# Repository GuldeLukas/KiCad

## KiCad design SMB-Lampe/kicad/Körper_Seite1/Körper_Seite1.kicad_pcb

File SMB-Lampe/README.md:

# README – SMB-Lampe (KiCad-Projekt)

- **Version / Stand:** 09.03.26
- **Verantwortliche Person / Team:** Lukas Gulde
- **Softwareversionen:** verwendete KiCad-Version 9.0
- **Fertigungsstatus:** Prototyp, Dokumentation nicht abgeschlossen
- **Lizenz / Nutzungsrechte:** 
- **Änderungshistorie:** 

## Projektübersicht
Dieses Verzeichnis enthält die Konstruktionsdaten des Projekts **SMB-Lampe**. Die Dateien liegen als **KiCad-Projekte** vor und umfassen Schaltpläne, Platinenentwürfe sowie projektbezogene Bibliotheken und Zusatzdateien.

## Speicherort der Projektdateien
Die relevanten Projektdateien des Programms **SMB-Lampe** sind unter folgendem Pfad verzeichnet:

- `KiCad-master/SMB-Lampe/kicad/`

Dort befinden sich unter anderem die Hauptprojektdateien:

- `SMB-Lampe.kicad_pro` – KiCad-Projektdatei

## Teilprojekte / Unterordner für Platinenentwürfe
Die jeweiligen Schaltpläne und Platinenentwürfe der einzelnen Baugruppen befinden sich in den folgenden Unterordnern:

- `Hauptplatine`
- `Hinterbein_hinten_Seite1_LED-P`
- `Hinterbein_hinten_Seite2_LED-P`
- `Hinterbein_vorne_Seite1_LED-P`
- `Hinterbein_vorne_Seite2_LED-P`
- `Körper_Seite1` 
- `Körper_Seite2` 

In diesen Ordnern liegen jeweils die zugehörigen KiCad-Dateien, typischerweise:

- `*.kicad_pro` – Projektdatei
- `*.kicad_sch` – Schaltplan
- `*.kicad_pcb` – Platinenlayout
- `*.kicad_prl` – projektspezifische Layout-/Darstellungseinstellungen

Teilweise sind zusätzlich weitere Fertigungs- oder 3D-Daten vorhanden, z. B.:

- `*.step` – 3D-Modell
- `*.gbrjob` – Gerber-Jobdatei

## Bibliotheken und Zusatzdaten
Zusätzliche projektbezogene Bibliotheken und Referenzdaten befinden sich in folgenden Verzeichnissen:

- `KiCad-master/Lib/` – benutzerdefinierte Bibliotheken
- `KiCad-master/Footprints/` – Footprint-Bibliotheken
- `KiCad-master/Datasheet/` – Datenblätter und Referenzunterlagen

Diese Ordner können für das korrekte Laden von Symbolen, Footprints und Zusatzinformationen in KiCad erforderlich sein.

## Empfohlene Verwendung
Zum Öffnen des Projekts wird **KiCad 9.x** empfohlen. Vorgehensweise:

1. KiCad starten.
2. Die Datei `SMB-Lampe.kicad_pro` öffnen.
3. Für einzelne Baugruppen bei Bedarf die jeweilige `*.kicad_pro`-Datei im entsprechenden Unterordner öffnen.

## Zweck dieses README
Dieses README dient der schnellen Orientierung innerhalb der Projektstruktur und erleichtert das Auffinden von:

- Hauptprojektdatei
- Schaltplänen
- Platinenlayouts
- Teilprojekten einzelner Baugruppen
- Bibliotheken und Zusatzdateien

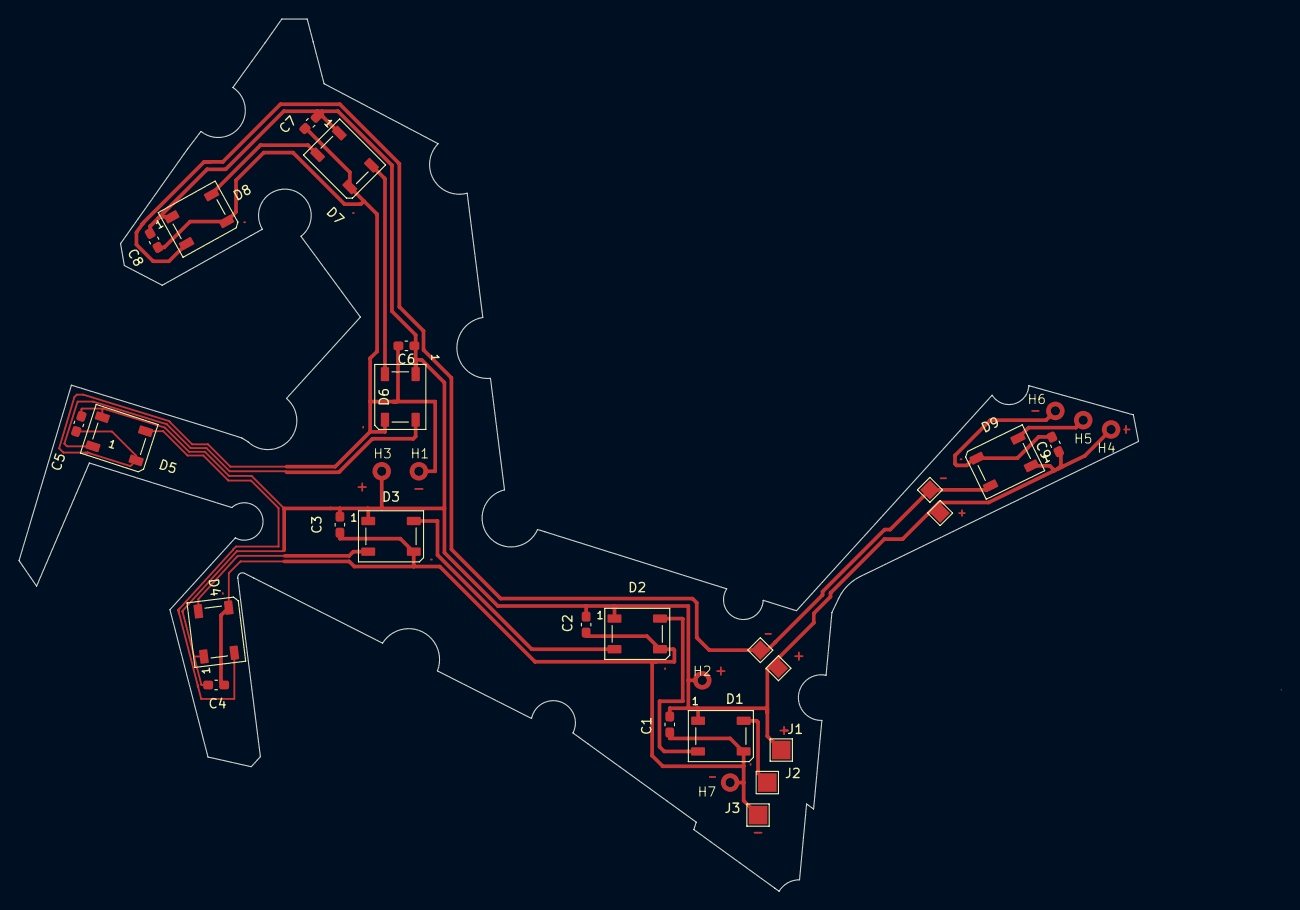
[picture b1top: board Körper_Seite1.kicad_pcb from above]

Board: 2 copper layers, 120.5 x 93.9 mm, 28 parts (0 on the bottom side), 12 nets.

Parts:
C1, C2, C3, C4, C5, C6, C7, C8, C9: 100nF; C_0603_1608Metric_Pad1.08x0.95mm_HandSolder
D1, D2, D3, D4, D5, D6, D7, D8, D9: WS2812B; LED_WS2812B_PLCC4_5.0x5.0mm_P3.2mm
H1, H2, H3, H4, H5, H6, H7: MountingHole_Pad; MountingHole D2 x d1 test
J1, J2, J3: Conn_01x01_Pin; TestPoint_Pad_2.0x2.0mm

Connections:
+5V: C1.1, C2.1, C3.1, C4.1, C5.1, C6.1, C7.1, C8.1, C9.1, D1.1 (VDD), D2.1 (VDD), D3.1 (VDD), D4.1 (VDD), D5.1 (VDD), D6.1 (VDD), D7.1 (VDD), D8.1 (VDD), D9.1 (VDD), H2.1, H3.1, H4.1, J1.1
/Data_In__Hinterbein_hinten_Seite2: D1.4 (DIN), J2.1
/Data_OUT_Körper_Seite2: D9.2 (DOUT), H5.1
Data: D5.2 (DOUT), D6.4 (DIN)
GND: C1.2, C2.2, C3.2, C4.2, C5.2, C6.2, C7.2, C8.2, C9.2, D1.3 (VSS), D2.3 (VSS), D3.3 (VSS), D4.3 (VSS), D5.3 (VSS), D6.3 (VSS), D7.3 (VSS), D8.3 (VSS), D9.3 (VSS), H1.1, H6.1, H7.1, J3.1
unnamed: D1.2 (DOUT), D2.4 (DIN)
unnamed: D2.2 (DOUT), D3.4 (DIN)
unnamed: D3.2 (DOUT), D4.4 (DIN)
unnamed: D4.2 (DOUT), D5.4 (DIN)
unnamed: D6.2 (DOUT), D7.4 (DIN)
unnamed: D7.2 (DOUT), D8.4 (DIN)
unnamed: D8.2 (DOUT), D9.4 (DIN)

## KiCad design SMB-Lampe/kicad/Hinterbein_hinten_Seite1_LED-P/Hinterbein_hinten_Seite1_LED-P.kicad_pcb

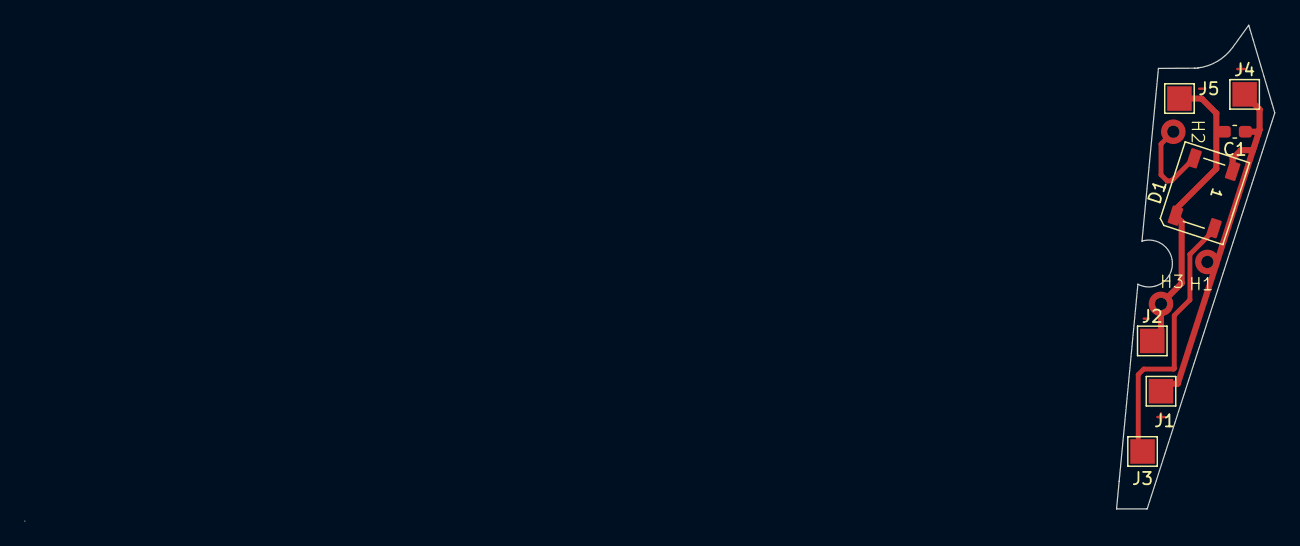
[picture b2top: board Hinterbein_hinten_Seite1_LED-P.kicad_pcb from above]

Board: 2 copper layers, 12.9 x 39.3 mm, 10 parts (0 on the bottom side), 4 nets.

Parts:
C1: 100nF; C_0603_1608Metric_Pad1.08x0.95mm_HandSolder
D1: WS2812B; LED_WS2812B_PLCC4_5.0x5.0mm_P3.2mm
H1, H2, H3: MountingHole_Pad; MountingHole D2 x d1 test
J1, J2, J3, J4, J5: Conn_01x01_Pin; TestPoint_Pad_2.0x2.0mm

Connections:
/+5V_IN_Hauptplatine: C1.1, D1.1 (VDD), H1.1, J1.1, J4.1
/Data_IN_Hauptplatine: D1.4 (DIN), J3.1
/Data_OUT_Hinterbein_hinten_Seite2: D1.2 (DOUT), H2.1
GND: C1.2, D1.3 (VSS), H3.1, J2.1, J5.1

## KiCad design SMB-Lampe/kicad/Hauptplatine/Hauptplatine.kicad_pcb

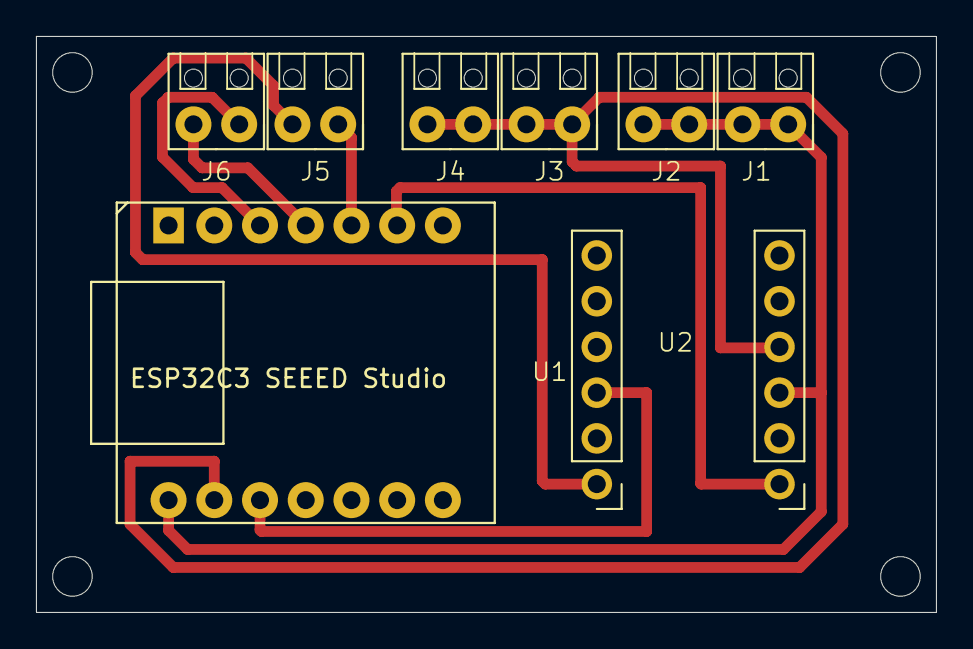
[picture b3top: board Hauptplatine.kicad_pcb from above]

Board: 2 copper layers, 50.0 x 32.0 mm, 8 parts (0 on the bottom side), 8 nets.

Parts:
J1, J2, J3, J4, J5, J6: Screw_Terminal_01x02; Screw Terminal
U1: ESP32C3 SEEED Studio; ESP32 C3
U2: 4-Kanal-I2C Pegelwandler; I2C Levelshifter

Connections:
+3.3V: U1.12 (3V3), U2.3 (LV)
+5V: J1.1, J1.2, J2.1, J2.2, U1.14 (5V), U2.9 (HV)
/ECHO_Ultraschall: J5.2, U2.1 (LV1)
/TRIG_Ultraschall: J5.1, U1.5 (PA8_A4_D4_SDA)
Data_LED: J6.2, U1.4 (PA11_A3_D3)
GND: J3.1, J3.2, J4.1, J4.2, U1.13 (GND), U2.10 (GND)
unnamed: U1.6 (PA9_A5_D5_SCL), U2.7 (HV1)
Steuer_Servo: J6.1, U1.3 (PA10_A2_D2)

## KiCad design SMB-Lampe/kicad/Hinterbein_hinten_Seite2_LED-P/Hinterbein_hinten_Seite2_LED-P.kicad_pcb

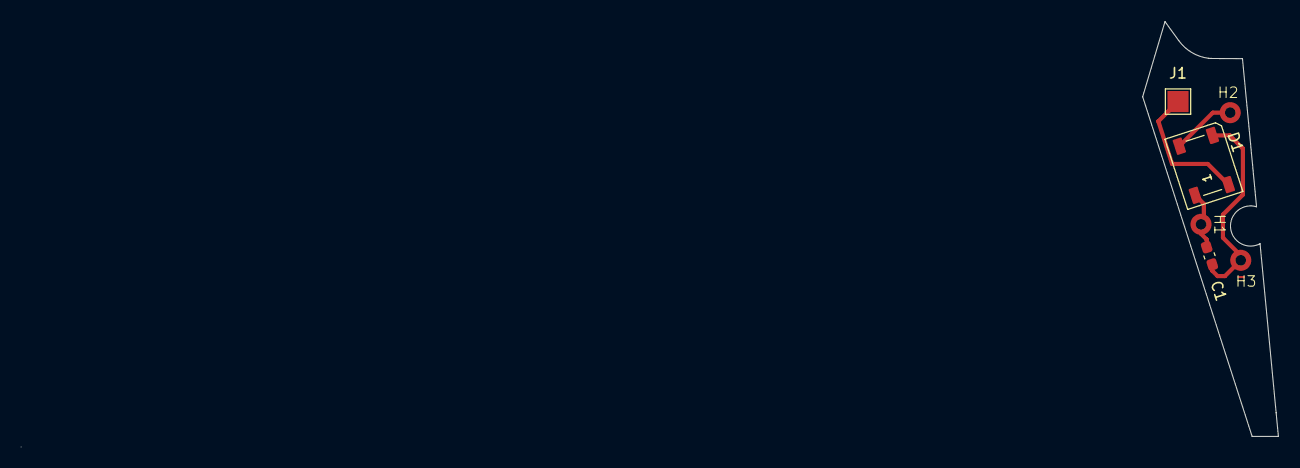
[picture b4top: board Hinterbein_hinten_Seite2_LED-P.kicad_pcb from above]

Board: 2 copper layers, 12.9 x 39.3 mm, 6 parts (0 on the bottom side), 4 nets.

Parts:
C1: 100nF; C_0603_1608Metric_Pad1.08x0.95mm_HandSolder
D1: WS2812B; LED_WS2812B_PLCC4_5.0x5.0mm_P3.2mm
H1, H2, H3: MountingHole_Pad; MountingHole D2 x d1 test
J1: Conn_01x01_Pin; TestPoint_Pad_2.0x2.0mm

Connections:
/+5V_IN_Hinterbein_hinten_Seite1: C1.1, D1.1 (VDD), H1.1
/Data_IN_Hinterbein_hinten_Seite1: D1.4 (DIN), H2.1
/Data_OUT_Körper_Seite1: D1.2 (DOUT), J1.1
GND: C1.2, D1.3 (VSS), H3.1

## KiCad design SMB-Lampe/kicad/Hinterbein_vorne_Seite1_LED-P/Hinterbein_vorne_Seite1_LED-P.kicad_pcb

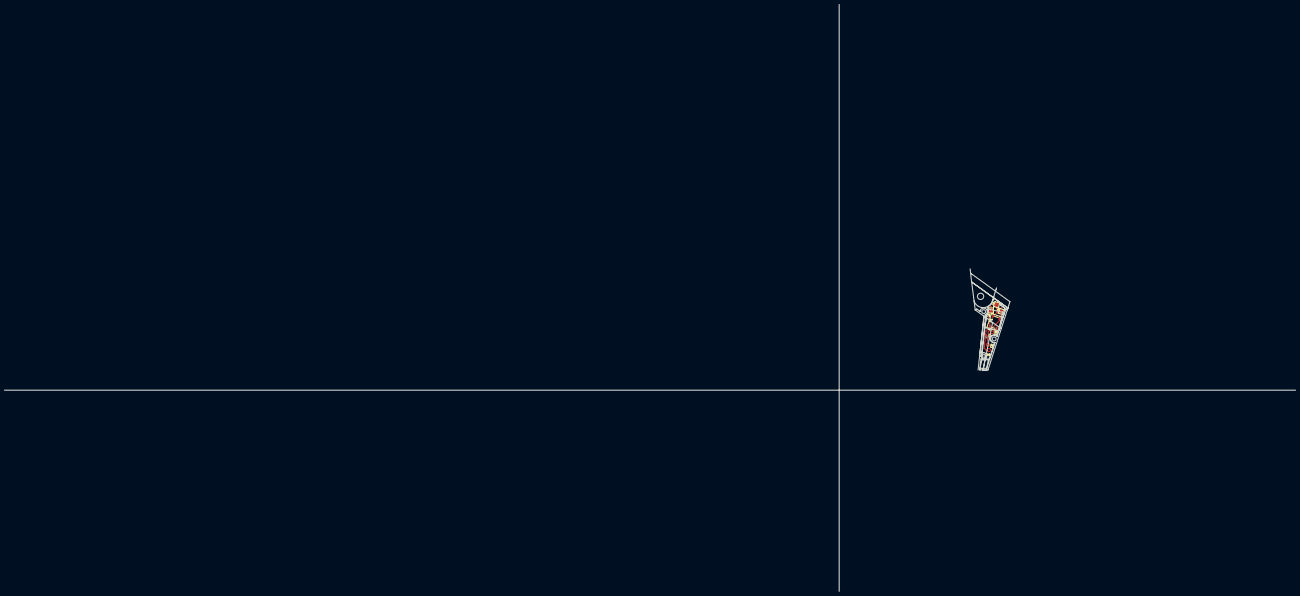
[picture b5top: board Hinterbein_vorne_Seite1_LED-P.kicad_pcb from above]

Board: 2 copper layers, 11.5 x 29.2 mm, 8 parts (0 on the bottom side), 4 nets.

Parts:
C1: 100nF; C_0603_1608Metric_Pad1.08x0.95mm_HandSolder
D1: WS2812B; LED_WS2812B_PLCC4_5.0x5.0mm_P3.2mm
H1, H2, H3: MountingHole_Pad; MountingHole D2 x d1 test
J1, J2, J3: Conn_01x01_Pin; TestPoint_Pad_2.0x2.0mm

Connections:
/+5V_IN_Körper_Seite2: C1.1, D1.1 (VDD), H1.1, J1.1
/Data_IN_Körper_Seite2: D1.4 (DIN), J2.1
/Data_OUT_Hinterbein_vorne_Seite2: D1.2 (DOUT), H2.1
GND: C1.2, D1.3 (VSS), H3.1, J3.1

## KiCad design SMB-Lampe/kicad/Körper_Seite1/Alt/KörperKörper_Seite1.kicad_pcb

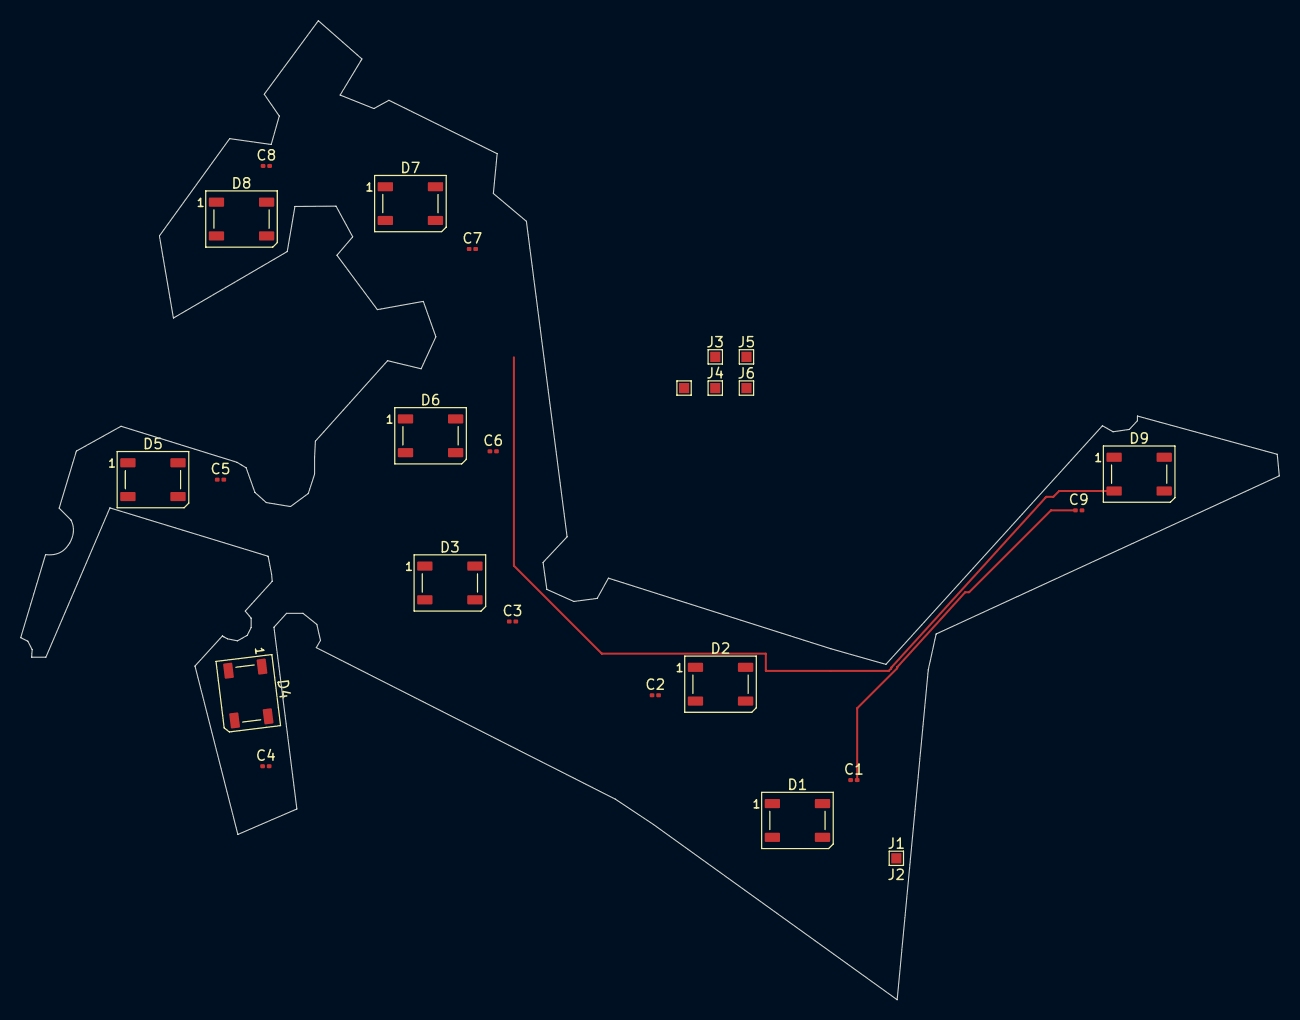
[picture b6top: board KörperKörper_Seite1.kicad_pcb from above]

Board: 2 copper layers, 123.0 x 95.7 mm, 24 parts (0 on the bottom side), 11 nets.

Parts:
C1, C2, C3, C4, C5, C6, C7, C8, C9: 100nF; C_0201_0603Metric
D1, D2, D3, D4, D5, D6, D7, D8, D9: WS2812B; LED_WS2812B_PLCC4_5.0x5.0mm_P3.2mm
J1, J2, J3, J4, J5, J6: Conn_01x01_Pin; TestPoint_Pad_1.0x1.0mm

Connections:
+5V: C1.1, C1.2, C2.1, C2.2, C3.1, C3.2, C4.1, C4.2, C5.1, C5.2, C6.1, C6.2, C7.1, C7.2, C8.1, C8.2, C9.1, C9.2, D1.1 (VDD), D1.3 (VSS), D2.1 (VDD), D2.3 (VSS), D3.1 (VDD), D3.3 (VSS), D4.1 (VDD), D4.3 (VSS), D5.1 (VDD), D5.3 (VSS), D6.1 (VDD), D6.3 (VSS), D7.1 (VDD), D7.3 (VSS), D8.1 (VDD), D8.3 (VSS), D9.1 (VDD), D9.3 (VSS), J1.1, J3.1, J4.1, J6.1
/Data_In: D1.2 (DOUT), J2.1
/Data_OUT: D9.4 (DIN), J5.1
Data: D5.4 (DIN), D6.2 (DOUT)
unnamed: D1.4 (DIN), D2.2 (DOUT)
unnamed: D2.4 (DIN), D3.2 (DOUT)
unnamed: D3.4 (DIN), D4.2 (DOUT)
unnamed: D4.4 (DIN), D5.2 (DOUT)
unnamed: D6.4 (DIN), D7.2 (DOUT)
unnamed: D7.4 (DIN), D8.2 (DOUT)
unnamed: D8.4 (DIN), D9.2 (DOUT)

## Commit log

2025-12-28 Erster Commit des Projekts
    Added KiCAD symbol and footprint for Seeeduino XIAO ESP32C3, an Eagle board and schematic, a pinout Excel sheet, and initial SMB-Lampe project files including KiCAD project, PCB, and schematic. These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
2025-12-28 Spannungsversorgung zu ESP hinzugefügt
2026-01-02 Beidseitige Platine Für hinteres Hinterbein
2026-01-02 Hauptplatine skizziert
    Bezeichner stimmen noch nicht
2026-01-06 Alle Platinen erstellt
    Alle Platinen wurden im Projekt einzeln erstellt.
2026-01-07 Alle LEDs nochmal richtig angeschlossen
2026-01-08 Platine für Körper Seite 1 erfolgreich erstellt
    Die Platine wurde mit der alten Außenkontur erstellt und fast komplett erfolgreich die Leiterbahnen erstellt.
2026-01-09 Hinterbein Seite 1/2 erstellt
    Anschlüsse zwischen den Platinen mit MountingHoles. Eigenes MountingHole Erstellt
2026-01-09 Hinterbein Hinten fertig
    Seite 1 und Seite 2 von Hinterbein hinten Sind fertig
2026-01-10 Vorderseite Platine Körper Seite 1 fertig
    zwei GND Verbindungen fehlen noch
2026-01-10 Körper mit Vorder und Rückseite fertig
    Alle Leiterbahnen sind gelegt und Verbindungen zu den anderen Platinen platziert
2026-01-12 Vorderes Hinterbein fertig
    Alle Platinen sind fertig beschaltet
2026-01-19 Hinterbeine Geändert teilweiße Körper
2026-01-20 Alle Platinen sind fertig zur Fertigung
    Aus diesem Stand folgt das erste fertig leuchtende Pferd
2026-01-25 Hauptplatine fertig
    Hauptplatine mit ESP Levelshifter und Screwsockets
2026-03-09 Nachträgliche Änderungen für die Fertigung und Präsentation
2026-03-09 Readme
2026-03-22 vor Schaltplananpassung
2026-03-24 Änderungen für Dokumentation
